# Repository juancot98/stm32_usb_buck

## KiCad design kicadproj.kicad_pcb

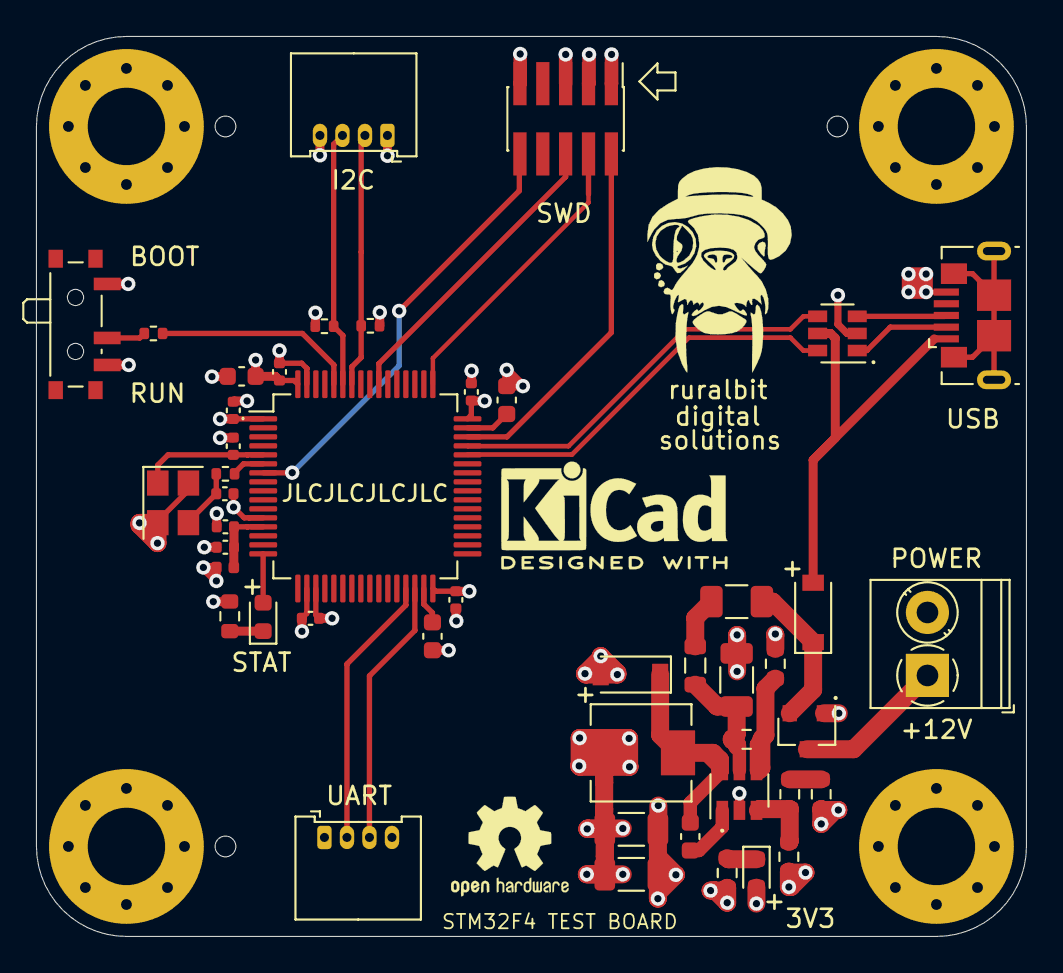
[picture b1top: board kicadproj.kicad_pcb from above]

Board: 4 copper layers, 55.0 x 50.0 mm, 51 parts (0 on the bottom side), 35 nets.

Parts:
C1: 4u7; C_0603_1608Metric
C2, C4: 2u2; C_0603_1608Metric
C3, C5, C6, C8, C9: 100n; C_0402_1005Metric
C7, C14, C16: 10u; C_1206_3216Metric
C10: 1u; C_0402_1005Metric
C11: 10n; C_0402_1005Metric
C12: 10n; C_0603_1608Metric
C13, C15: 12p; C_0402_1005Metric
D1, D2: B5819W; D_SOD-123
D3: Blue; LED_0603_1608Metric
D4: Red; LED_0603_1608Metric
F1: 250mA; Fuse_1206_3216Metric
FB1: 600 @ 600MHz; L_0805_2012Metric
H1, H2, H3, H4: MountingHole_Pad; MountingHole_4.3mm_M4_Pad_Via
J1: PWR; TerminalBlock_Phoenix_PT-1,5-2-3.5-H_1x02_P3.50mm_Horizontal
J2: I2C; Molex_PicoBlade_53048-0410_1x04_P1.25mm_Horizontal
J3: SWD; PinHeader_2x05_P1.27mm_Vertical_SMD
J4: USART; Molex_PicoBlade_53048-0410_1x04_P1.25mm_Horizontal
J5: USB_B_Micro; USB_Micro-B_GCT_USB3076-30-A
L1: 39n; L_0402_1005Metric
L2: 10u; L_Sunlord_MWSA0518_5.4x5.2mm
Q1: AO3401A; SOT-23
R1: 100k; R_0603_1608Metric
R2: 68k; R_0603_1608Metric
R3, R8: 2k2; R_0402_1005Metric
R4: 47k; R_0603_1608Metric
R5: 15k; R_0603_1608Metric
R6: 270; R_0603_1608Metric
R7: 10k; R_0402_1005Metric
R9: 1k5; R_0603_1608Metric
R10: 47; R_0402_1005Metric
R11: 1k; R_0603_1608Metric
SW1: SW_SPDT; SW_SPDT_PCM12
U1: STM32F405RGT6; LQFP-64_10x10mm_P0.5mm
U2: MP2359; SOT-23-6
U3: USBLC6-2SC6; SOT-23-6
Y1: 16MHz; Crystal_SMD_3225-4Pin_3.2x2.5mm
e: OSHW-Logo2_7.3x6mm_SilkScreen

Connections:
+3.3VA: C10.1, C11.1, L1.1, U1.13
+3V3: C1.1, C3.1, C5.1, C6.1, C8.1, C9.1, C14.1, C16.1, D4.2, J2.1, J3.1, J4.1, L1.2, L2.2, R3.2, R4.2, R8.2, SW1.1, U1.1, U1.19, U1.32, U1.48, U1.64
+5V: D1.2, J5.1, U3.5
+12V: J1.1, Q1.3
BOOT0: R7.2, U1.60
BUCK_BST: C12.2, U2.1
BUCK_EN: R1.1, R2.2, U2.4
BUCK_FB: R4.1, R5.2, U2.3
BUCK_IN: C7.1, FB1.1, R1.2, U2.5
BUCK_SW: C12.1, D2.1, L2.1, U2.6
GND: C1.2, C2.2, C3.2, C4.2, C5.2, C6.2, C7.2, C8.2, C9.2, C10.2, C11.2, C13.2, C14.2, C15.2, C16.2, D2.2, H1.1, H2.1, H3.1, H4.1, J1.2, J2.4, J3.3, J3.5, J3.9, J4.4, J5.5, Q1.1, R2.1, R6.1, R9.1, R11.1, SW1.3, U1.12, U1.18, U1.63, U2.2, U3.2, Y1.2, Y1.4
HSE_IN: C13.1, U1.5, Y1.1
HSE_OUT: R10.2, U1.6
I2C1_SCL: J2.2, R8.1, U1.58
I2C1_SDA: J2.3, R3.1, U1.59
LED_STATUS: D3.2, U1.16
NRST: J3.10, U1.7
unnamed: C2.1, U1.31
unnamed: C4.1, U1.47
unnamed: C15.1, R10.1, Y1.3
unnamed: D1.1, F1.2, Q1.2
unnamed: D3.1, R9.2
unnamed: D4.1, R11.2
unnamed: F1.1, FB1.2
unnamed: R5.1, R6.2
unnamed: R7.1, SW1.2
SWCLK: J3.4, U1.49
SWDIO: J3.2, U1.46
SWO: J3.6, U1.55
USART3_RX: J4.3, U1.30
USART3_TX: J4.2, U1.29
USB_CONN_D+: J5.3, U3.3
USB_CONN_D-: J5.2, U3.1
USB_D+: U1.45, U3.4
USB_D-: U1.44, U3.6
